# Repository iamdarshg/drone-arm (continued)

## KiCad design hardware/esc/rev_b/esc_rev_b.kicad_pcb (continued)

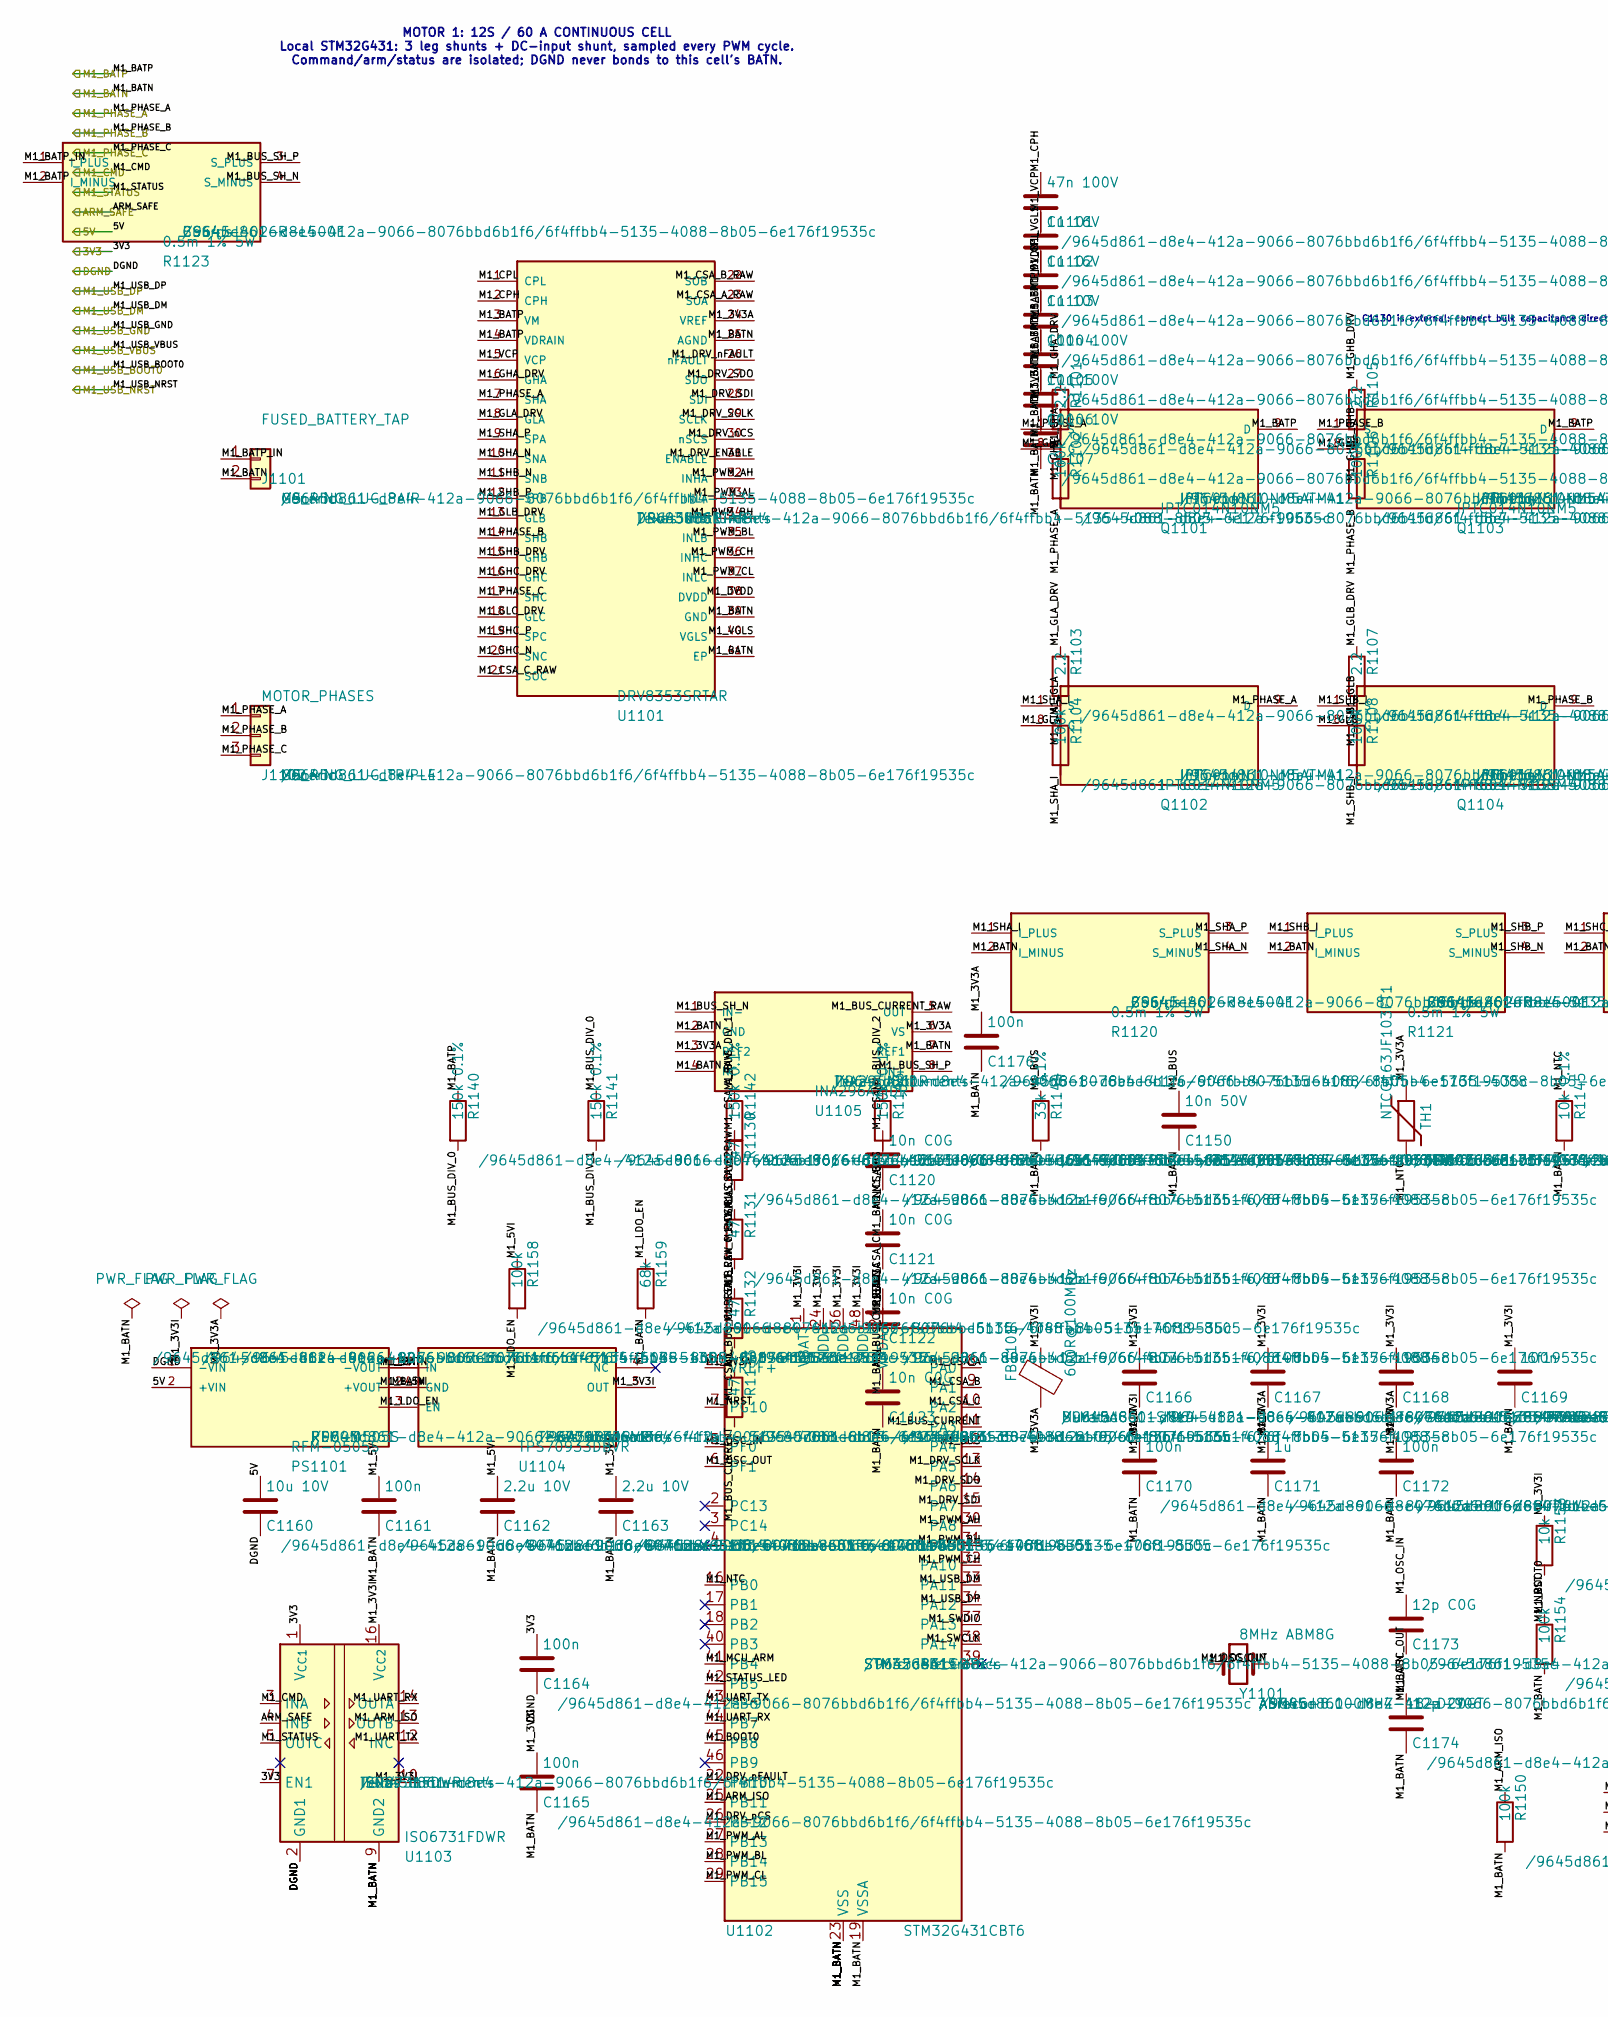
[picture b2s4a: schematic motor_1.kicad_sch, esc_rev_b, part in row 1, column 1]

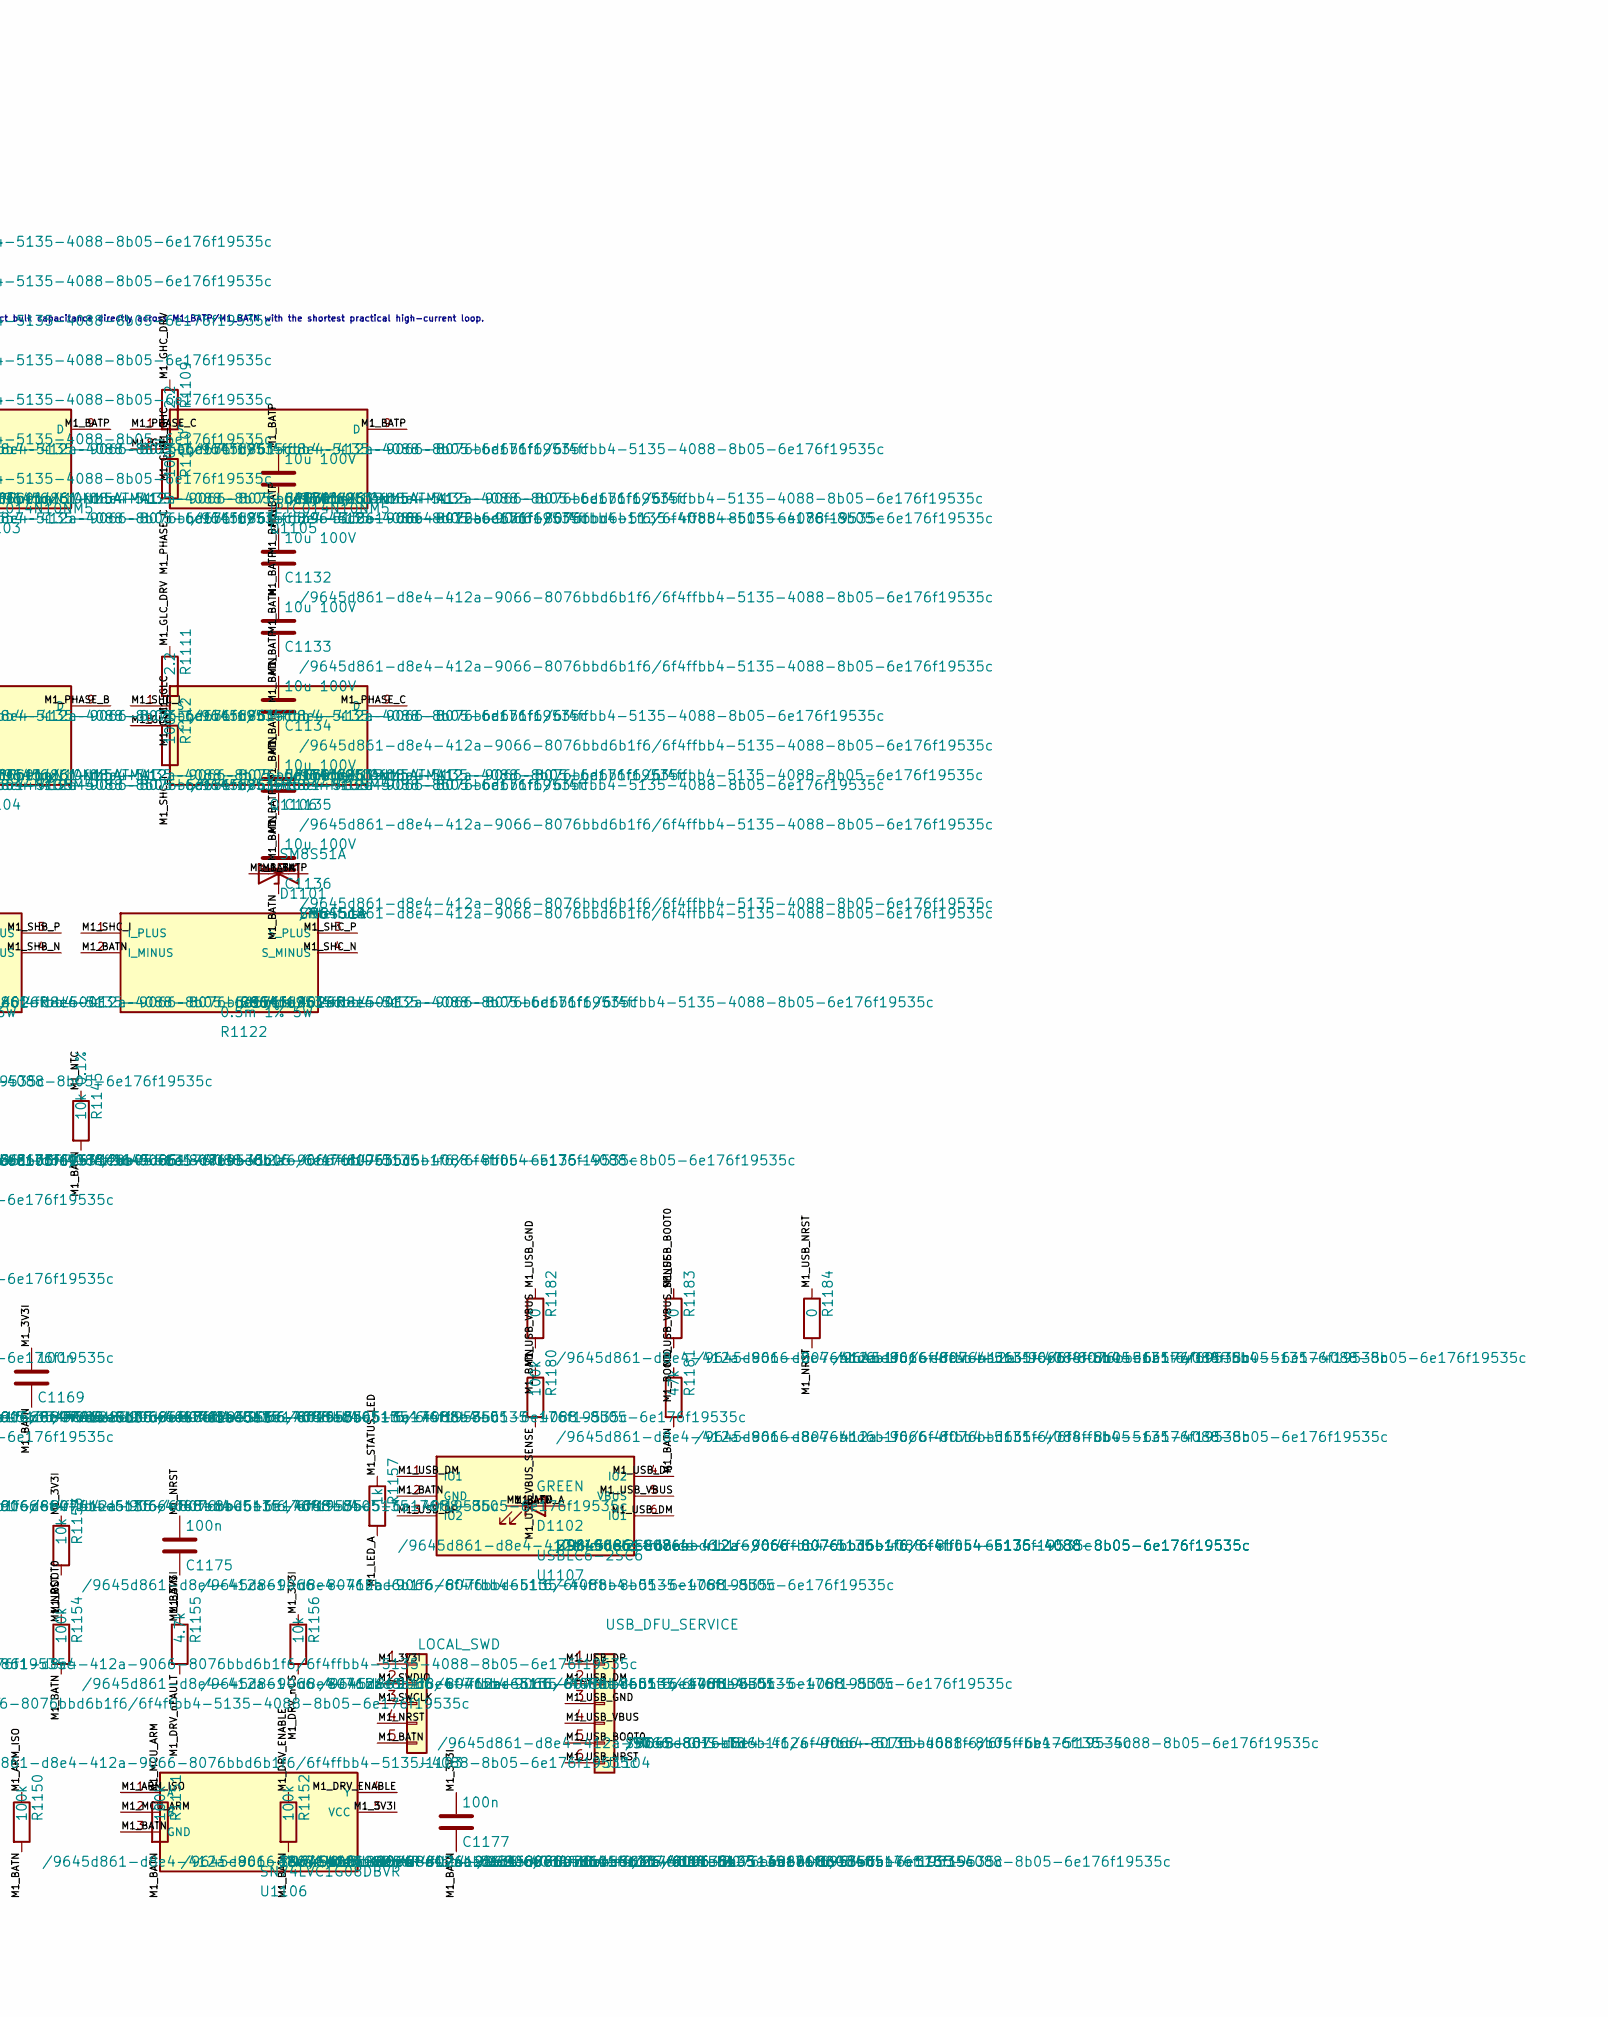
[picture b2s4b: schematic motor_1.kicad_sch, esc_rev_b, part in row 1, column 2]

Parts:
C1101: 47n 100V; C_0603_1608Metric
C1102, C1103: 1u 16V; C_0603_1608Metric
C1104: 1u 10V; C_0603_1608Metric
C1105: 100n 100V; C_0603_1608Metric
C1106, C1131, C1132, C1133, C1134, C1135, C1136: 10u 100V; C_1210_3225Metric
C1107: 100n 10V; C_0603_1608Metric
C1120, C1121, C1122, C1123: 10n C0G; C_0603_1608Metric
C1150: 10n 50V; C_0603_1608Metric
C1160: 10u 10V; C_0805_2012Metric
C1161, C1164, C1165, C1175, C1176, C1177: 100n; C_0603_1608Metric
C1162, C1163: 2.2u 10V; C_0603_1608Metric
C1166: 4.7u; C_0603_1608Metric
C1167, C1168, C1169, C1170, C1172: 100n; C_0402_1005Metric
C1171: 1u; C_0603_1608Metric
C1173, C1174: 12p C0G; C_0402_1005Metric
D1101: SM8S51A; DO-218AB_SM8S; MPN SM8S51A
D1102: GREEN; LED_0603_1608Metric
FB1101: 600R@100MHz; L_0603_1608Metric; MPN BLM18AG601SN1D
J1101: FUSED_BATTERY_TAP; POWER_LUG_M5_2P_P20; MPN M5_RING_LUG_PAIR
J1102: MOTOR_PHASES; POWER_LUG_M5_3P_P20; MPN M5_RING_LUG_TRIPLE
J1103: LOCAL_SWD; PinHeader_1x05_P1.27mm_Vertical
J1104: USB_DFU_SERVICE; JST_GH_SM06B-GHS-TB_1x06-1MP_P1.25mm_Horizontal; MPN SM06B-GHS-TB
PS1101: RFM-0505S; RFM_SIP4_11.5x6_P2.54; MPN RFM-0505S
Q1101, Q1102, Q1103, Q1104, Q1105, Q1106: IPTC014N10NM5; PG-HDSOP-16_TOLT_IPTC; MPN IPTC014N10NM5ATMA1
R1101, R1103, R1105, R1107, R1109, R1111: 2.2; R_0603_1608Metric
R1102, R1104, R1106, R1108, R1110, R1112, R1150, R1151, R1152, R1154, R1158, R1180: 100k; R_0603_1608Metric
R1120, R1121, R1122, R1123: 0.5m 1% 5W; CSS4J-4026_Kelvin; MPN CSS4J-4026R-L500F
R1130, R1131, R1132, R1133: 47; R_0603_1608Metric
R1140, R1141, R1142, R1143: 150k 0.1%; R_1206_3216Metric
R1144: 33k 0.1%; R_0603_1608Metric
R1145: 10k 0.1%; R_0603_1608Metric
R1153, R1156: 10k; R_0603_1608Metric
R1155: 4.7k; R_0603_1608Metric
R1157: 1k; R_0603_1608Metric
R1159: 68k; R_0603_1608Metric
R1181: 47k; R_0603_1608Metric
R1182, R1183, R1184: 0; R_0603_1608Metric
TH1: NTCG163JF103FT1; R_0603_1608Metric; MPN NTCG163JF103FT1
U1101: DRV8353SRTAR; WQFN-40-EP_6x6_P0.5; MPN DRV8353SRTAR
U1102: STM32G431CBT6; LQFP-48_7x7mm_P0.5mm; MPN STM32G431CBT6
U1103: ISO6731FDWR; SOIC-16W_7.5x10.3mm_P1.27mm; MPN ISO6731FDWR
U1104: TPS70933DBVR; SOT-23-5; MPN TPS70933DBVR
U1105: INA296A2IDR; SOIC-8_3.9x4.9mm_P1.27mm; MPN INA296A2IDR
U1106: SN74LVC1G08DBVR; SOT-23-5; MPN SN74LVC1G08DBVR
U1107: USBLC6-2SC6; SOT-23-6; MPN USBLC6-2SC6
Y1101: 8MHz ABM8G; Crystal_SMD_3225-4Pin_3.2x2.5mm; MPN ABM8G-8.000MHZ-18-D2Y-T

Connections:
/3V3: C1164.1, U1103.1 (V_{CC1}), U1103.7 (EN1); also elsewhere on the board
/5V: C1160.1, PS1101.2 (+VIN); also elsewhere on the board
/ARM_SAFE: U1103.4 (INB); also elsewhere on the board
/DGND: C1160.2, C1164.2, PS1101.1 (-VIN), U1103.2 (GND1), U1103.8 (GND1); also elsewhere on the board
/M1_BATN: C1103.2, C1104.2, C1105.2, C1106.2, C1107.2, C1120.2, C1121.2, C1122.2, C1123.2, C1131.2, C1132.2, C1133.2, C1134.2, C1135.2, C1136.2, C1150.2, C1161.2, C1162.2, C1163.2, C1165.2, C1166.2, C1167.2, C1168.2, C1169.2, C1170.2, C1171.2, C1172.2, C1173.2, C1174.2, C1175.2, C1176.2, C1177.2, D1101.1 (A1), D1102.1 (K), J1101.2, J1103.5, PS1101.3 (-VOUT), R1120.2 (I_MINUS), R1121.2 (I_MINUS), R1122.2 (I_MINUS), R1144.2, R1145.2, R1150.2, R1151.2, R1152.2, R1154.2, R1159.2, R1181.2, R1182.2, U1101.25 (AGND), U1101.39 (GND), U1101.41 (EP), U1102.19 (VSSA), U1102.23 (VSS), U1102.35 (VSS), U1102.47 (VSS), U1103.9 (GND2), U1103.15 (GND2), U1104.2 (GND), U1105.2 (GND), U1105.4 (NC), U1105.7 (REF1), U1106.3 (GND), U1107.2 (GND); also elsewhere on the board
/M1_BATP: C1102.2, C1105.1, C1106.1, C1131.1, C1132.1, C1133.1, C1134.1, C1135.1, C1136.1, D1101.2 (A2), Q1101.9 (D), Q1103.9 (D), Q1105.9 (D), R1123.2 (I_MINUS), R1140.1, U1101.3 (VM), U1101.4 (VDRAIN); also elsewhere on the board
/M1_CMD: U1103.3 (INA); also elsewhere on the board
/M1_PHASE_A: J1102.1, Q1101.1 (S), Q1102.9 (D), R1102.2, U1101.7 (SHA)
/M1_PHASE_B: J1102.2, Q1103.1 (S), Q1104.9 (D), R1106.2, U1101.14 (SHB)
/M1_PHASE_C: J1102.3, Q1105.1 (S), Q1106.9 (D), R1110.2, U1101.17 (SHC)
/M1_STATUS: U1103.5 (OUTC); also elsewhere on the board
/Motor 1 power cell/M1_3V3A: C1107.1, C1171.1, C1172.1, C1176.1, FB1101.2, TH1.1, U1101.24 (VREF), U1102.20 (VREF+), U1102.21 (VDDA), U1105.3 (REF2), U1105.6 (VS)
/Motor 1 power cell/M1_3V3I: C1163.1, C1165.1, C1166.1, C1167.1, C1168.1, C1169.1, C1170.1, C1177.1, FB1101.1, J1103.1, R1153.1, R1155.1, R1156.1, U1102.1 (VBAT), U1102.24 (VDD), U1102.36 (VDD), U1102.48 (VDD), U1103.10 (EN2), U1103.16 (V_{CC2}), U1104.5 (OUT), U1106.5 (VCC)
/Motor 1 power cell/M1_5VI: C1161.1, C1162.1, PS1101.4 (+VOUT), R1158.1, U1104.1 (IN)
/Motor 1 power cell/M1_ARM_ISO: R1150.1, U1102.25 (PB11), U1103.13 (OUTB), U1106.1 (A)
/Motor 1 power cell/M1_BATP_IN: J1101.1, R1123.1 (I_PLUS)
/Motor 1 power cell/M1_BOOT0: R1154.1, R1183.2, U1102.45 (PB8)
/Motor 1 power cell/M1_BUS: C1150.1, R1143.2, R1144.1, U1102.12 (PA4)
/Motor 1 power cell/M1_BUS_CURRENT: C1123.1, R1133.2, U1102.11 (PA3)
/Motor 1 power cell/M1_BUS_CURRENT_RAW: R1133.1, U1105.5 (OUT)
/Motor 1 power cell/M1_BUS_DIV_0: R1140.2, R1141.1
/Motor 1 power cell/M1_BUS_DIV_1: R1141.2, R1142.1
/Motor 1 power cell/M1_BUS_DIV_2: R1142.2, R1143.1
/Motor 1 power cell/M1_BUS_SH_N: R1123.4 (S_MINUS), U1105.1 (IN-)
/Motor 1 power cell/M1_BUS_SH_P: R1123.3 (S_PLUS), U1105.8 (IN+)
/Motor 1 power cell/M1_CPH: C1101.1, U1101.2 (CPH)
/Motor 1 power cell/M1_CPL: C1101.2, U1101.1 (CPL)
/Motor 1 power cell/M1_CSA_A: C1120.1, R1130.2, U1102.8 (PA0)
/Motor 1 power cell/M1_CSA_A_RAW: R1130.1, U1101.23 (SOA)
/Motor 1 power cell/M1_CSA_B: C1121.1, R1131.2, U1102.9 (PA1)
/Motor 1 power cell/M1_CSA_B_RAW: R1131.1, U1101.22 (SOB)
/Motor 1 power cell/M1_CSA_C: C1122.1, R1132.2, U1102.10 (PA2)
/Motor 1 power cell/M1_CSA_C_RAW: R1132.1, U1101.21 (SOC)
/Motor 1 power cell/M1_DRV_ENABLE: R1152.1, U1101.31 (ENABLE), U1106.4 (Y)
/Motor 1 power cell/M1_DRV_SCLK: U1101.29 (SCLK), U1102.13 (PA5)
/Motor 1 power cell/M1_DRV_SDI: U1101.28 (SDI), U1102.15 (PA7)
/Motor 1 power cell/M1_DRV_SDO: U1101.27 (SDO), U1102.14 (PA6)
/Motor 1 power cell/M1_DRV_nCS: R1156.2, U1101.30 (nSCS), U1102.26 (PB12)
/Motor 1 power cell/M1_DRV_nFAULT: R1155.2, U1101.26 (nFAULT), U1102.22 (PB10)
/Motor 1 power cell/M1_DVDD: C1104.1, U1101.38 (DVDD)
/Motor 1 power cell/M1_GHA: Q1101.8 (G), R1101.2, R1102.1
/Motor 1 power cell/M1_GHA_DRV: R1101.1, U1101.6 (GHA)
/Motor 1 power cell/M1_GHB: Q1103.8 (G), R1105.2, R1106.1
/Motor 1 power cell/M1_GHB_DRV: R1105.1, U1101.15 (GHB)
/Motor 1 power cell/M1_GHC: Q1105.8 (G), R1109.2, R1110.1
/Motor 1 power cell/M1_GHC_DRV: R1109.1, U1101.16 (GHC)
/Motor 1 power cell/M1_GLA: Q1102.8 (G), R1103.2, R1104.1
/Motor 1 power cell/M1_GLA_DRV: R1103.1, U1101.8 (GLA)
/Motor 1 power cell/M1_GLB: Q1104.8 (G), R1107.2, R1108.1
/Motor 1 power cell/M1_GLB_DRV: R1107.1, U1101.13 (GLB)
/Motor 1 power cell/M1_GLC: Q1106.8 (G), R1111.2, R1112.1
/Motor 1 power cell/M1_GLC_DRV: R1111.1, U1101.18 (GLC)
/Motor 1 power cell/M1_LDO_EN: R1158.2, R1159.1, U1104.3 (EN)
/Motor 1 power cell/M1_LED_A: D1102.2 (A), R1157.2
/Motor 1 power cell/M1_MCU_ARM: R1151.1, U1102.41 (PB4), U1106.2 (B)
/Motor 1 power cell/M1_NRST: C1175.1, J1103.4, R1153.2, R1184.2, U1102.7 (PG10)
/Motor 1 power cell/M1_NTC: R1145.1, TH1.2, U1102.16 (PB0)
/Motor 1 power cell/M1_OSC_IN: C1173.1, U1102.5 (PF0), Y1101.1
/Motor 1 power cell/M1_OSC_OUT: C1174.1, U1102.6 (PF1), Y1101.2
/Motor 1 power cell/M1_PWM_AH: U1101.32 (INHA), U1102.30 (PA8)
/Motor 1 power cell/M1_PWM_AL: U1101.33 (INLA), U1102.27 (PB13)
/Motor 1 power cell/M1_PWM_BH: U1101.34 (INHB), U1102.31 (PA9)
/Motor 1 power cell/M1_PWM_BL: U1101.35 (INLB), U1102.28 (PB14)
/Motor 1 power cell/M1_PWM_CH: U1101.36 (INHC), U1102.32 (PA10)
/Motor 1 power cell/M1_PWM_CL: U1101.37 (INLC), U1102.29 (PB15)
/Motor 1 power cell/M1_SHA_I: Q1102.1 (S), R1104.2, R1120.1 (I_PLUS)
/Motor 1 power cell/M1_SHA_N: R1120.4 (S_MINUS), U1101.10 (SNA)
/Motor 1 power cell/M1_SHA_P: R1120.3 (S_PLUS), U1101.9 (SPA)
/Motor 1 power cell/M1_SHB_I: Q1104.1 (S), R1108.2, R1121.1 (I_PLUS)
/Motor 1 power cell/M1_SHB_N: R1121.4 (S_MINUS), U1101.11 (SNB)
/Motor 1 power cell/M1_SHB_P: R1121.3 (S_PLUS), U1101.12 (SPB)
/Motor 1 power cell/M1_SHC_I: Q1106.1 (S), R1112.2, R1122.1 (I_PLUS)
/Motor 1 power cell/M1_SHC_N: R1122.4 (S_MINUS), U1101.20 (SNC)
/Motor 1 power cell/M1_SHC_P: R1122.3 (S_PLUS), U1101.19 (SPC)
/Motor 1 power cell/M1_STATUS_LED: R1157.1, U1102.42 (PB5)
/Motor 1 power cell/M1_SWCLK: J1103.3, U1102.38 (PA14)
/Motor 1 power cell/M1_SWDIO: J1103.2, U1102.37 (PA13)
/Motor 1 power cell/M1_UART_RX: U1102.44 (PB7), U1103.14 (OUTA)
/Motor 1 power cell/M1_UART_TX: U1102.43 (PB6), U1103.12 (INC)
/Motor 1 power cell/M1_USB_DM: J1104.2, U1102.33 (PA11), U1107.1 (IO1), U1107.6 (IO1)
/Motor 1 power cell/M1_USB_DP: J1104.1, U1102.34 (PA12), U1107.3 (IO2), U1107.4 (IO2)
/Motor 1 power cell/M1_USB_VBUS: J1104.4, R1180.1, U1107.5 (VBUS)
/Motor 1 power cell/M1_USB_VBUS_SENSE: R1180.2, R1181.1
/Motor 1 power cell/M1_VCP: C1102.1, U1101.5 (VCP)
/Motor 1 power cell/M1_VGLS: C1103.1, U1101.40 (VGLS)
unnamed: J1104.3, R1182.1
unnamed: J1104.5, R1183.1
unnamed: J1104.6, R1184.1

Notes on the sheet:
MOTOR 1: 12S / 60 A CONTINUOUS CELL Local STM32G431: 3 leg shunts + DC-input shunt, sampled every PWM cycle. Command/arm/status are isolated; DGND never bonds to this cell's BATN.
C1130 is external: connect bulk capacitance directly across M1_BATP/M1_BATN with the shortest practical high-current loop.
